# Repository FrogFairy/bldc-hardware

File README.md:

## Schematic top level

## Layout -made with KiCad!-

## 3D views

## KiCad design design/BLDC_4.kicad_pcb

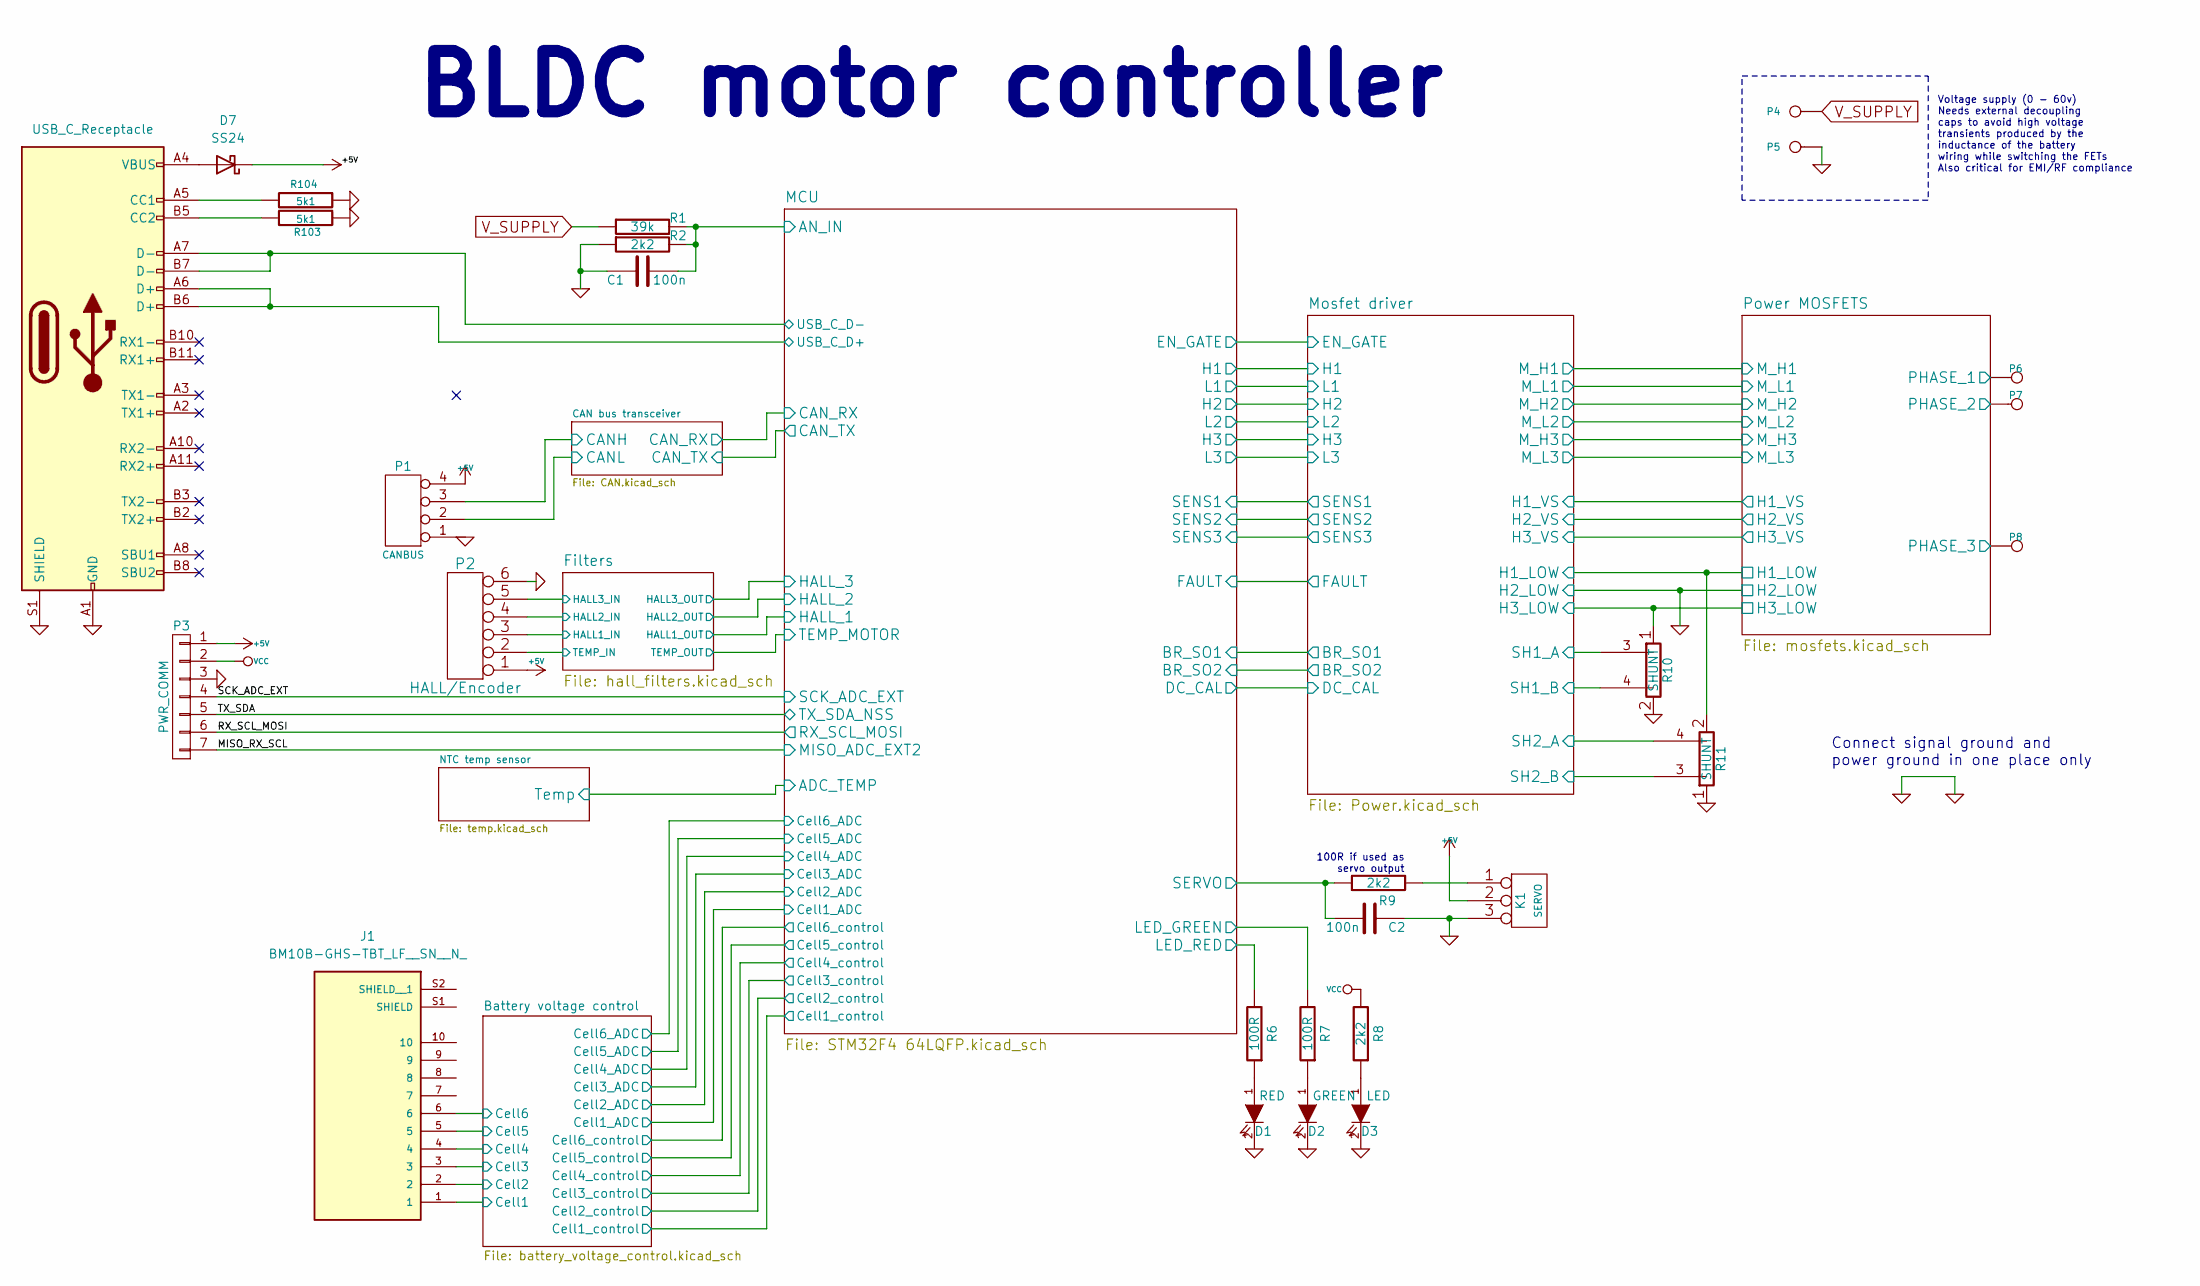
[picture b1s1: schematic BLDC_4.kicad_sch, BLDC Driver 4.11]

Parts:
C1, C2: 100n; SMD-0603_c
D1: RED; LED-0603
D2: GREEN; LED-0603
D3: LED; LED-0603
D7: SS24; D_SMA
J1: BM10B-GHS-TBT_LF__SN__N_; JST_BM10B-GHS-TBT_LF__SN__N_; PARTREV N/A
J2: USB_C_Receptacle
K1: SERVO; pinhead-1X03
P1: CANBUS; b4b-ph-kl
P2: HALL/Encoder; MICRO_JST_6
P3: PWR_COMM; b7b-ph-kl
P4: IN+; 1PAD_4x5mm
P5: IN-; 1PAD_4x5mm
P6: MOTOR3; 1PAD_4x5mm
P7: MOTOR2; 1PAD_4x5mm
P8: MOTOR1; 1PAD_4x5mm
R1: 39k; SMD-0603_r
R2, R8, R9: 2k2; SMD-0603_r
R6, R7: 100R; SMD-0603_r
R10, R11: SHUNT; WSLP2726
R103, R104: 5k1; SMD-0603_r

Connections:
+5V: D7.1 (K), K1.2 (PM), P1.4, P2.1, P3.1; also elsewhere on the board
/Battery voltage control/Cell1: J1.1; also elsewhere on the board
/Battery voltage control/Cell2: J1.2; also elsewhere on the board
/Battery voltage control/Cell3: J1.3; also elsewhere on the board
/Battery voltage control/Cell4: J1.4; also elsewhere on the board
/Battery voltage control/Cell5: J1.5; also elsewhere on the board
/Battery voltage control/Cell6: J1.6; also elsewhere on the board
/CAN bus transceiver/CANH: P1.3; also elsewhere on the board
/CAN bus transceiver/CANL: P1.2; also elsewhere on the board
/Filters/HALL1_IN: P2.3; also elsewhere on the board
/Filters/HALL2_IN: P2.4; also elsewhere on the board
/Filters/HALL3_IN: P2.5; also elsewhere on the board
/Filters/TEMP_MOTOR: P2.2; also elsewhere on the board
/MCU/AN_IN: C1.2, R1.2, R2.2; also elsewhere on the board
/MCU/LED_GREEN: R7.2; also elsewhere on the board
/MCU/LED_RED: R6.2; also elsewhere on the board
/MCU/SERVO: C2.2, R9.1; also elsewhere on the board
/MISO_RX_SCL: P3.7; also elsewhere on the board
/Mosfet driver/H1_LOW: R11.2; also elsewhere on the board
/Mosfet driver/H1_VS: P6.1; also elsewhere on the board
/Mosfet driver/H2_VS: P7.1; also elsewhere on the board
/Mosfet driver/H3_LOW: R10.1; also elsewhere on the board
/Mosfet driver/H3_VS: P8.1; also elsewhere on the board
/Mosfet driver/SH1_A: R10.3; also elsewhere on the board
/Mosfet driver/SH1_B: R10.4; also elsewhere on the board
/Mosfet driver/SH2_A: R11.4; also elsewhere on the board
/Mosfet driver/SH2_B: R11.3; also elsewhere on the board
/RX_SCL_MOSI: P3.6; also elsewhere on the board
/SCK_ADC_EXT: P3.4; also elsewhere on the board
/TX_SDA: P3.5; also elsewhere on the board
GND: C1.1, C2.1, D1.2 (K), D2.2 (K), D3.2 (K), J2.A1 (GND), J2.A12 (GND), J2.B1 (GND), J2.B12 (GND), J2.S1 (SHIELD), K1.3, P1.1, P2.6, P3.3, P5.1, R2.1, R10.2, R11.1, R103.1, R104.1; also elsewhere on the board
unnamed: D1.1 (A), R6.1
unnamed: D2.1 (A), R7.1
unnamed: D3.1 (A), R8.1
unnamed: D7.2 (A), J2.A4 (VBUS), J2.A9 (VBUS), J2.B4 (VBUS), J2.B9 (VBUS)
unnamed: J2.A5 (CC1), R104.2
unnamed: J2.B5 (CC2), R103.2
unnamed: J2.A6 (D+), J2.B6 (D+)
unnamed: J2.A7 (D-), J2.B7 (D-)
unnamed: K1.1, R9.2
VCC: P3.2, R8.2; also elsewhere on the board
V_SUPPLY: P4.1, R1.1; also elsewhere on the board

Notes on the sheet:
Voltage supply (0 - 60v) Needs external decoupling caps to avoid high voltage transients produced by the inductance of the battery wiring while switching the FETs Also critical for EMI/RF compliance
Connect signal ground and power ground in one place only
BLDC motor controller
100R if used as servo output

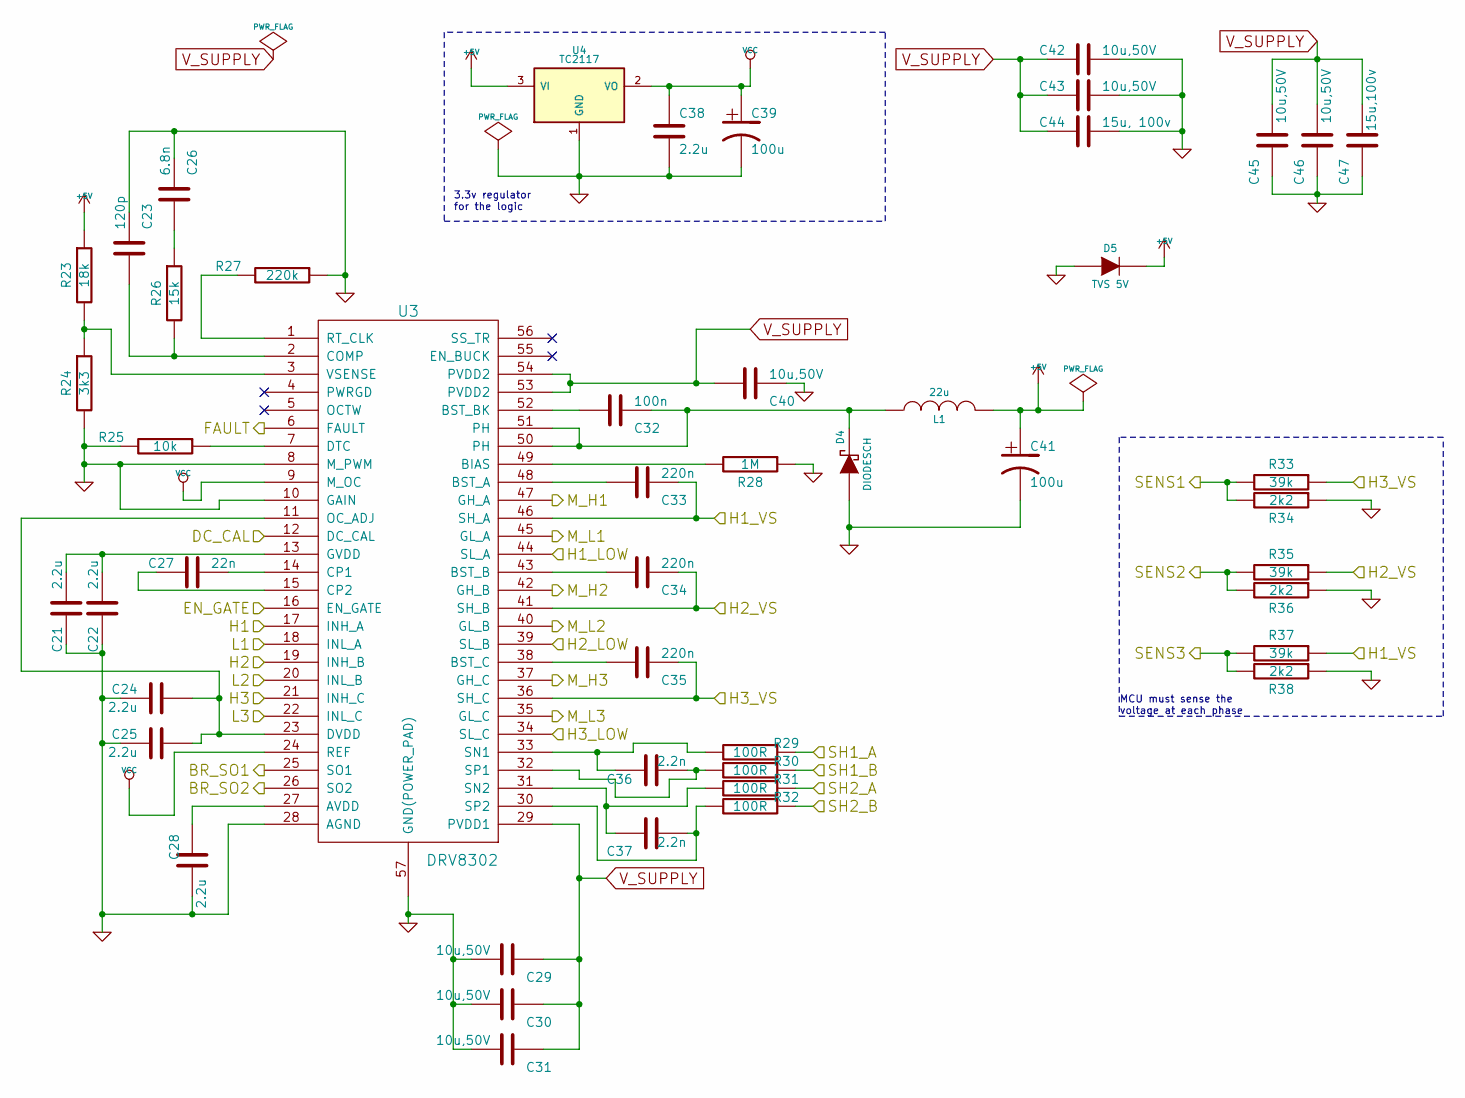
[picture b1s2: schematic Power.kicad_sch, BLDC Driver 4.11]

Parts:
C21, C22, C24, C25, C28, C38: 2.2u; SMD-0603_c
C23: 120p; SMD-0603_c
C26: 6.8n; SMD-0603_c
C27: 22n; SMD-0603_c
C29, C30, C31, C40, C42, C43, C45, C46: 10u,50V; SMD-1206
C32: 100n; SMD-0603_c
C33, C34, C35: 220n; SMD-0603_c
C36, C37: 2.2n; SMD-0603_c
C39, C41: 100u; c_tant_B
C44: 15u, 100v; c_2220
C47: 15u,100v; c_2220
D4: DIODESCH; SMA_Handsoldering
D5: TVS 5V; do214ac
L1: 22u; inductor_smd_8x5mm
R23: 18k; SMD-0603_r
R24: 3k3; SMD-0603_r
R25: 10k; SMD-0603_r
R26: 15k; SMD-0603_r
R27: 220k; SMD-0603_r
R28: 1M; SMD-0603_r
R29, R30, R31, R32: 100R; SMD-0603_r
R33, R35, R37: 39k; SMD-0603_r
R34, R36, R38: 2k2; SMD-0603_r
U3: DRV8302; TSSOP-56-PP
U4: TC2117; SOT-223

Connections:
+5V: C41.1, D5.2 (K), L1.2, R23.1, U4.3 (VI); also elsewhere on the board
/MCU/BR_SO1: U3.25 (SO1); also elsewhere on the board
/MCU/BR_SO2: U3.26 (SO2); also elsewhere on the board
/MCU/DC_CAL: U3.12 (DC_CAL); also elsewhere on the board
/MCU/EN_GATE: U3.16 (EN_GATE); also elsewhere on the board
/MCU/FAULT: U3.6 (FAULT); also elsewhere on the board
/MCU/H1: U3.17 (INH_A); also elsewhere on the board
/MCU/H2: U3.19 (INH_B); also elsewhere on the board
/MCU/H3: U3.21 (INH_C); also elsewhere on the board
/MCU/L1: U3.18 (INL_A); also elsewhere on the board
/MCU/L2: U3.20 (INL_B); also elsewhere on the board
/MCU/L3: U3.22 (INL_C); also elsewhere on the board
/MCU/SENS1: R33.2, R34.2; also elsewhere on the board
/MCU/SENS2: R35.2, R36.2; also elsewhere on the board
/MCU/SENS3: R37.2, R38.2; also elsewhere on the board
/Mosfet driver/H1_LOW: U3.44 (SL_A); also elsewhere on the board
/Mosfet driver/H1_VS: C33.1, R37.1, U3.46 (SH_A); also elsewhere on the board
/Mosfet driver/H2_VS: C34.1, R35.1, U3.41 (SH_B); also elsewhere on the board
/Mosfet driver/H3_LOW: U3.34 (SL_C); also elsewhere on the board
/Mosfet driver/H3_VS: C35.1, R33.1, U3.36 (SH_C); also elsewhere on the board
/Mosfet driver/M_H1: U3.47 (GH_A); also elsewhere on the board
/Mosfet driver/M_H2: U3.42 (GH_B); also elsewhere on the board
/Mosfet driver/M_H3: U3.37 (GH_C); also elsewhere on the board
/Mosfet driver/M_L1: U3.45 (GL_A); also elsewhere on the board
/Mosfet driver/M_L2: U3.40 (GL_B); also elsewhere on the board
/Mosfet driver/M_L3: U3.35 (GL_C); also elsewhere on the board
/Mosfet driver/SH1_A: R29.1; also elsewhere on the board
/Mosfet driver/SH1_B: R30.1; also elsewhere on the board
/Mosfet driver/SH2_A: R31.1; also elsewhere on the board
/Mosfet driver/SH2_B: R32.1; also elsewhere on the board
GND: C21.2, C22.2, C23.1, C24.1, C25.1, C26.1, C28.1, C29.2, C30.2, C31.2, C38.2, C39.2, C40.1, C41.2, C42.1, C43.1, C44.1, C45.1, C46.1, C47.1, D4.1 (A), D5.1 (A), R24.2, R25.2, R27.1, R28.1, R34.1, R36.1, R38.1, U3.8 (M_PWM), U3.10 (GAIN), U3.28 (AGND), U3.39 (SL_B), U3.57 (GND(POWER_PAD)), U4.1 (GND); also elsewhere on the board
unnamed: C26.2, R26.1
unnamed: C32.1, D4.2 (K), L1.1, U3.50 (PH), U3.51 (PH)
unnamed: C28.2, U3.27 (AVDD)
unnamed: R28.2, U3.49 (BIAS)
unnamed: C33.2, U3.48 (BST_A)
unnamed: C34.2, U3.43 (BST_B)
unnamed: C32.2, U3.52 (BST_BK)
unnamed: C35.2, U3.38 (BST_C)
unnamed: C23.2, R26.2, U3.2 (COMP)
unnamed: C27.1, U3.14 (CP1)
unnamed: C27.2, U3.15 (CP2)
unnamed: R25.1, U3.7 (DTC)
unnamed: C24.2, C25.2, U3.11 (OC_ADJ), U3.23 (DVDD)
unnamed: C21.1, C22.1, U3.13 (GVDD)
unnamed: R27.2, U3.1 (RT_CLK)
unnamed: C36.1, R29.2, U3.33 (SN1)
unnamed: C37.1, R31.2, U3.31 (SN2)
unnamed: C36.2, R30.2, U3.32 (SP1)
unnamed: C37.2, R32.2, U3.30 (SP2)
unnamed: R23.2, R24.1, U3.3 (VSENSE)
VCC: C38.1, C39.1, U3.9 (M_OC), U3.24 (REF), U4.2 (VO); also elsewhere on the board
V_SUPPLY: C29.1, C30.1, C31.1, C40.2, C42.2, C43.2, C44.2, C45.2, C46.2, C47.2, U3.29 (PVDD1), U3.53 (PVDD2), U3.54 (PVDD2); also elsewhere on the board

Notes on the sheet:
MCU must sense the voltage at each phase
3.3v regulator for the logic

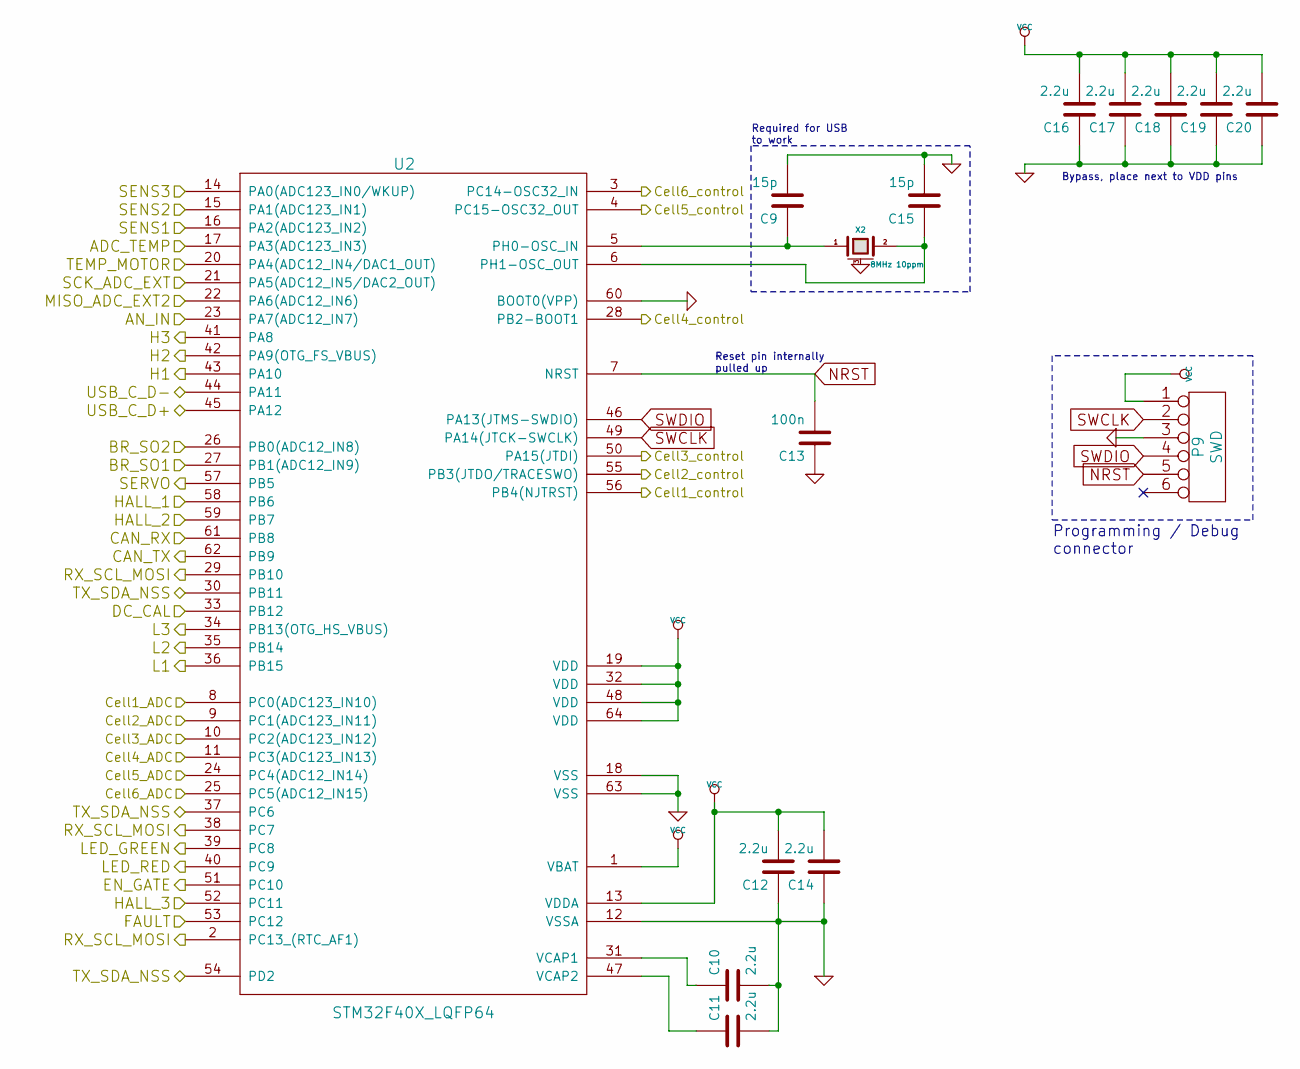
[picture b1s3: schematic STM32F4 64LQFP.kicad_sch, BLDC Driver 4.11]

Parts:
C9, C15: 15p; SMD-0603_c
C10, C11, C12, C14, C16, C17, C18, C19, C20: 2.2u; SMD-0603_c
C13: 100n; SMD-0603_c
P9: SWD; MICRO_JST_6
U2: STM32F40X_LQFP64; lqfp64_pad_mod
X2: 8MHz 10ppm; Crystal_5x3mm; mfg# ABM3B-8.0-10-1UT

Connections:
/Battery voltage control/Cell1_ADC: U2.8 (PC0(ADC123_IN10)); also elsewhere on the board
/Battery voltage control/Cell1_control: U2.56 (PB4(NJTRST)); also elsewhere on the board
/Battery voltage control/Cell2_ADC: U2.9 (PC1(ADC123_IN11)); also elsewhere on the board
/Battery voltage control/Cell2_control: U2.55 (PB3(JTDO/TRACESWO)); also elsewhere on the board
/Battery voltage control/Cell3_ADC: U2.10 (PC2(ADC123_IN12)); also elsewhere on the board
/Battery voltage control/Cell3_control: U2.50 (PA15(JTDI)); also elsewhere on the board
/Battery voltage control/Cell4_ADC: U2.11 (PC3(ADC123_IN13)); also elsewhere on the board
/Battery voltage control/Cell4_control: U2.28 (PB2-BOOT1); also elsewhere on the board
/Battery voltage control/Cell5_ADC: U2.24 (PC4(ADC12_IN14)); also elsewhere on the board
/Battery voltage control/Cell5_control: U2.4 (PC15-OSC32_OUT); also elsewhere on the board
/Battery voltage control/Cell6_ADC: U2.25 (PC5(ADC12_IN15)); also elsewhere on the board
/Battery voltage control/Cell6_control: U2.3 (PC14-OSC32_IN); also elsewhere on the board
/CAN bus transceiver/CAN_RX: U2.61 (PB8); also elsewhere on the board
/CAN bus transceiver/CAN_TX: U2.62 (PB9); also elsewhere on the board
/Filters/HALL1_OUT: U2.58 (PB6); also elsewhere on the board
/Filters/HALL2_OUT: U2.59 (PB7); also elsewhere on the board
/Filters/HALL3_OUT: U2.52 (PC11); also elsewhere on the board
/Filters/TEMP_MOTOR: U2.20 (PA4(ADC12_IN4/DAC1_OUT)); also elsewhere on the board
/MCU/ADC_TEMP: U2.17 (PA3(ADC123_IN3)); also elsewhere on the board
/MCU/AN_IN: U2.23 (PA7(ADC12_IN7)); also elsewhere on the board
/MCU/BR_SO1: U2.27 (PB1(ADC12_IN9)); also elsewhere on the board
/MCU/BR_SO2: U2.26 (PB0(ADC12_IN8)); also elsewhere on the board
/MCU/DC_CAL: U2.33 (PB12); also elsewhere on the board
/MCU/EN_GATE: U2.51 (PC10); also elsewhere on the board
/MCU/FAULT: U2.53 (PC12); also elsewhere on the board
/MCU/H1: U2.43 (PA10); also elsewhere on the board
/MCU/H2: U2.42 (PA9(OTG_FS_VBUS)); also elsewhere on the board
/MCU/H3: U2.41 (PA8); also elsewhere on the board
/MCU/L1: U2.36 (PB15); also elsewhere on the board
/MCU/L2: U2.35 (PB14); also elsewhere on the board
/MCU/L3: U2.34 (PB13(OTG_HS_VBUS)); also elsewhere on the board
/MCU/LED_GREEN: U2.39 (PC8); also elsewhere on the board
/MCU/LED_RED: U2.40 (PC9); also elsewhere on the board
/MCU/SENS1: U2.16 (PA2(ADC123_IN2)); also elsewhere on the board
/MCU/SENS2: U2.15 (PA1(ADC123_IN1)); also elsewhere on the board
/MCU/SENS3: U2.14 (PA0(ADC123_IN0/WKUP)); also elsewhere on the board
/MCU/SERVO: U2.57 (PB5); also elsewhere on the board
/MCU/USB_C_D+: U2.45 (PA12)
/MCU/USB_C_D-: U2.44 (PA11)
/MISO_RX_SCL: U2.22 (PA6(ADC12_IN6)); also elsewhere on the board
/RX_SCL_MOSI: U2.2 (PC13_(RTC_AF1)), U2.29 (PB10), U2.38 (PC7); also elsewhere on the board
/SCK_ADC_EXT: U2.21 (PA5(ADC12_IN5/DAC2_OUT)); also elsewhere on the board
/TX_SDA: U2.30 (PB11), U2.37 (PC6), U2.54 (PD2); also elsewhere on the board
GND: C9.2, C10.2, C11.2, C12.1, C13.1, C14.1, C15.2, C16.1, C17.1, C18.1, C19.1, C20.1, P9.3, U2.12 (VSSA), U2.18 (VSS), U2.60 (BOOT0(VPP)), U2.63 (VSS), X2.3 (case); also elsewhere on the board
NRST: C13.2, P9.5, U2.7 (NRST)
unnamed: C9.1, U2.5 (PH0-OSC_IN), X2.1
unnamed: C15.1, U2.6 (PH1-OSC_OUT), X2.2
unnamed: C10.1, U2.31 (VCAP1)
unnamed: C11.1, U2.47 (VCAP2)
SWCLK: P9.2, U2.49 (PA14(JTCK-SWCLK))
SWDIO: P9.4, U2.46 (PA13(JTMS-SWDIO))
VCC: C12.2, C14.2, C16.2, C17.2, C18.2, C19.2, C20.2, P9.1, U2.1 (VBAT), U2.13 (VDDA), U2.19 (VDD), U2.32 (VDD), U2.48 (VDD), U2.64 (VDD); also elsewhere on the board

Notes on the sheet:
Reset pin internally pulled up
Required for USB to work
Programming / Debug connector
Bypass, place next to VDD pins

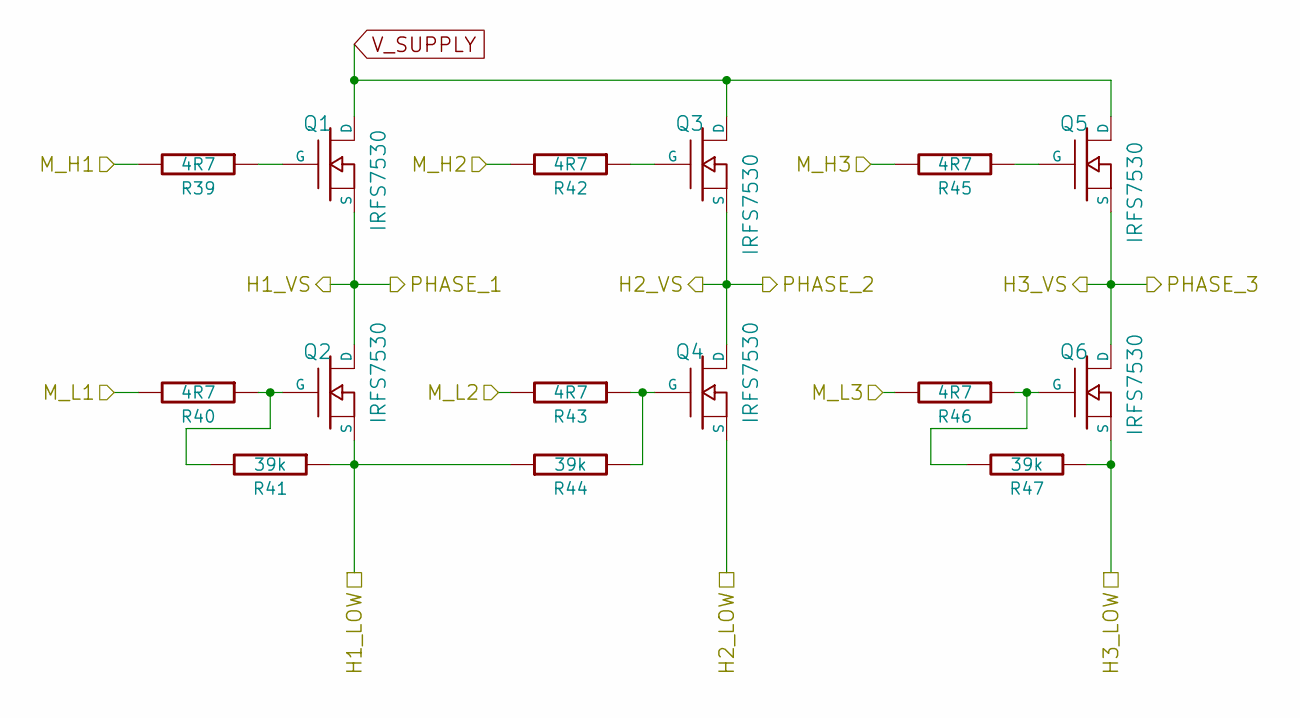
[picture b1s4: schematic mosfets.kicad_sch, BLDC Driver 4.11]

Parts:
Q1, Q2, Q3, Q4, Q5, Q6: IRFS7530; D2PAK-7-GDS
R39, R40, R42, R43, R45, R46: 4R7; SMD-0603_r
R41, R44, R47: 39k; SMD-0603_r

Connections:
/Mosfet driver/H1_LOW: Q2.S, R41.1, R44.1; also elsewhere on the board
/Mosfet driver/H1_VS: Q1.S, Q2.D; also elsewhere on the board
/Mosfet driver/H2_VS: Q3.S, Q4.D; also elsewhere on the board
/Mosfet driver/H3_LOW: Q6.S, R47.1; also elsewhere on the board
/Mosfet driver/H3_VS: Q5.S, Q6.D; also elsewhere on the board
/Mosfet driver/M_H1: R39.2; also elsewhere on the board
/Mosfet driver/M_H2: R42.2; also elsewhere on the board
/Mosfet driver/M_H3: R45.2; also elsewhere on the board
/Mosfet driver/M_L1: R40.2; also elsewhere on the board
/Mosfet driver/M_L2: R43.2; also elsewhere on the board
/Mosfet driver/M_L3: R46.2; also elsewhere on the board
GND: Q4.S; also elsewhere on the board
unnamed: Q1.G, R39.1
unnamed: Q2.G, R40.1, R41.2
unnamed: Q3.G, R42.1
unnamed: Q4.G, R43.1, R44.2
unnamed: Q5.G, R45.1
unnamed: Q6.G, R46.1, R47.2
V_SUPPLY: Q1.D, Q3.D, Q5.D; also elsewhere on the board

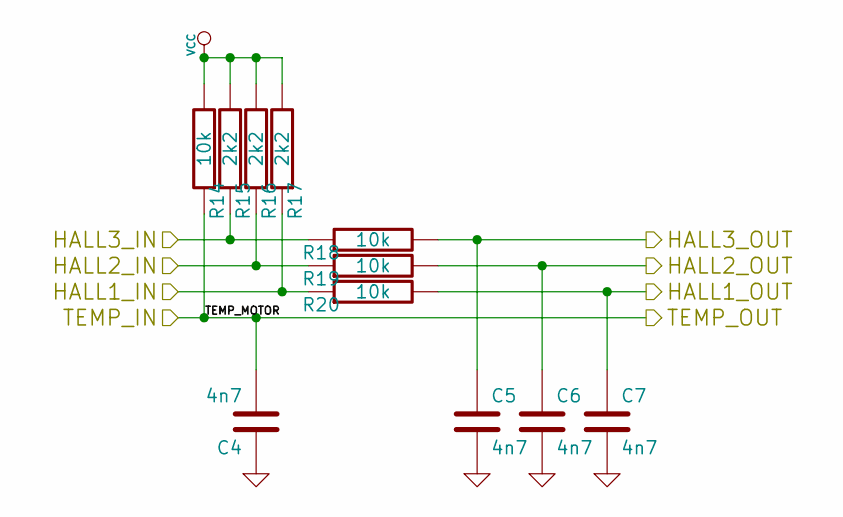
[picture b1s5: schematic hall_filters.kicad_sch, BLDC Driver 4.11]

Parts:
C4, C5, C6, C7: 4n7; SMD-0603_c
R14, R18, R19, R20: 10k; SMD-0603_r
R15, R16, R17: 2k2; SMD-0603_r

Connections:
/Filters/HALL1_IN: R17.1, R20.1; also elsewhere on the board
/Filters/HALL1_OUT: C7.1, R20.2; also elsewhere on the board
/Filters/HALL2_IN: R16.1, R19.1; also elsewhere on the board
/Filters/HALL2_OUT: C6.1, R19.2; also elsewhere on the board
/Filters/HALL3_IN: R15.1, R18.1; also elsewhere on the board
/Filters/HALL3_OUT: C5.1, R18.2; also elsewhere on the board
/Filters/TEMP_MOTOR: C4.2, R14.1; also elsewhere on the board
GND: C4.1, C5.2, C6.2, C7.2; also elsewhere on the board
VCC: R14.2, R15.2, R16.2, R17.2; also elsewhere on the board

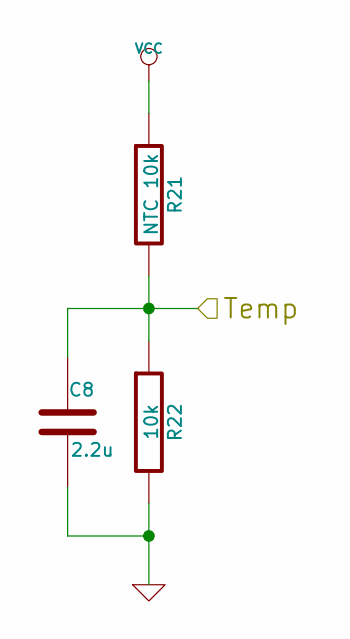
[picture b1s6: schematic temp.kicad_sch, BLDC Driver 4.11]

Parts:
C8: 2.2u; SMD-0603_c
R21: NTC 10k; SMD-0603_r
R22: 10k; SMD-0603_r

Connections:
/MCU/ADC_TEMP: C8.1, R21.2, R22.1; also elsewhere on the board
GND: C8.2, R22.2; also elsewhere on the board
VCC: R21.1; also elsewhere on the board

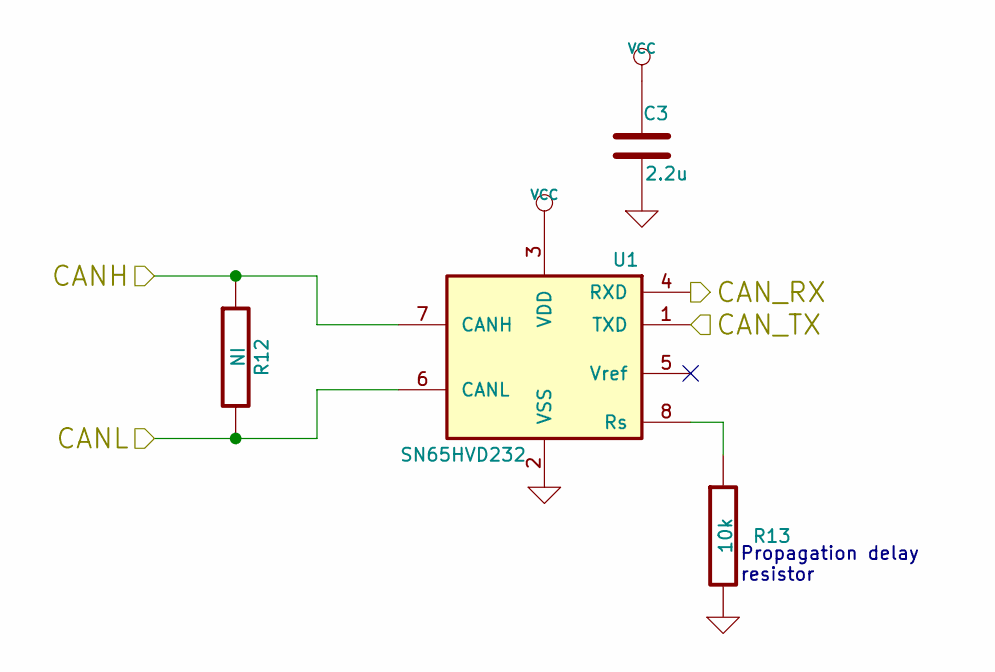
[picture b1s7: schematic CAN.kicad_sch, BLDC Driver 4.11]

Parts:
C3: 2.2u; SMD-0603_c
R12: NI; SMD-0603_r
R13: 10k; SMD-0603_r
U1: SN65HVD232; SOIC-8-W

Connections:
/CAN bus transceiver/CANH: R12.1, U1.7 (CANH); also elsewhere on the board
/CAN bus transceiver/CANL: R12.2, U1.6 (CANL); also elsewhere on the board
/CAN bus transceiver/CAN_RX: U1.4 (RXD); also elsewhere on the board
/CAN bus transceiver/CAN_TX: U1.1 (TXD); also elsewhere on the board
GND: C3.2, R13.2, U1.2 (VSS); also elsewhere on the board
unnamed: R13.1, U1.8 (Rs)
VCC: C3.1, U1.3 (VDD); also elsewhere on the board

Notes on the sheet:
Propagation delay resistor

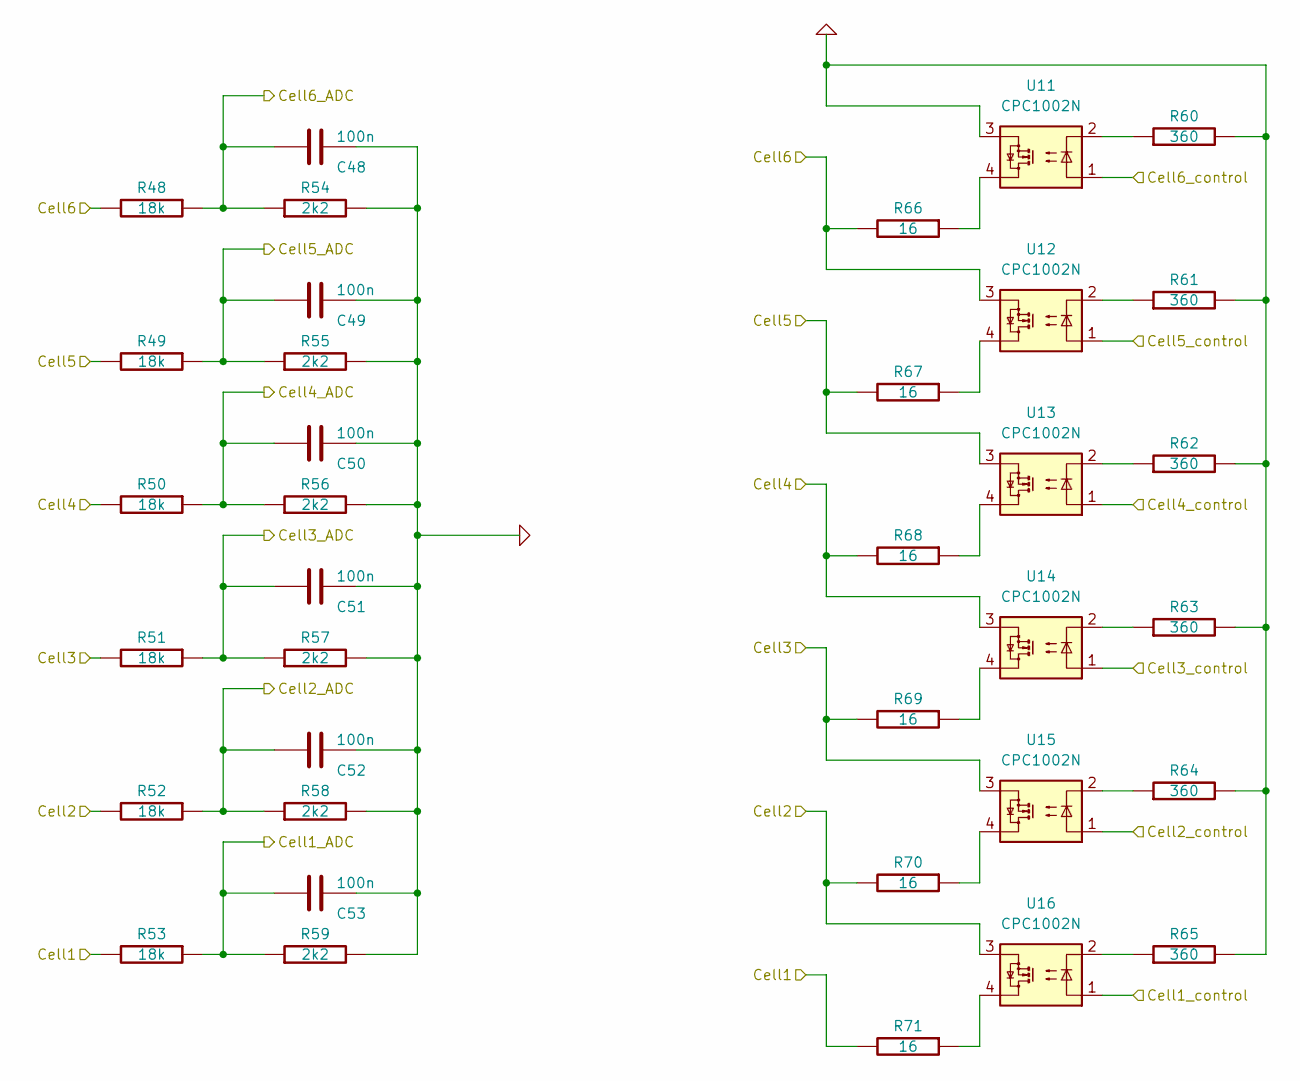
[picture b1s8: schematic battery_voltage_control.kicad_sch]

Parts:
C48, C49, C50, C51, C52, C53: 100n; SMD-0603_c
R48, R49, R50, R51, R52, R53: 18k; SMD-0603_r
R54, R55, R56, R57, R58, R59: 2k2; SMD-0603_r
R60, R61, R62, R63, R64, R65: 360; SMD-0603_r
R66, R67, R68, R69, R70, R71: 16; R_2512_6332Metric
U11, U12, U13, U14, U15, U16: CPC1002N; SOP-4_3.8x4.1mm_P2.54mm

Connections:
/Battery voltage control/Cell1: R53.2, R71.2; also elsewhere on the board
/Battery voltage control/Cell1_ADC: C53.2, R53.1, R59.1; also elsewhere on the board
/Battery voltage control/Cell1_control: U16.1; also elsewhere on the board
/Battery voltage control/Cell2: R52.2, R70.2, U16.3; also elsewhere on the board
/Battery voltage control/Cell2_ADC: C52.2, R52.1, R58.1; also elsewhere on the board
/Battery voltage control/Cell2_control: U15.1; also elsewhere on the board
/Battery voltage control/Cell3: R51.2, R69.2, U15.3; also elsewhere on the board
/Battery voltage control/Cell3_ADC: C51.2, R51.1, R57.1; also elsewhere on the board
/Battery voltage control/Cell3_control: U14.1; also elsewhere on the board
/Battery voltage control/Cell4: R50.2, R68.2, U14.3; also elsewhere on the board
/Battery voltage control/Cell4_ADC: C50.2, R50.1, R56.1; also elsewhere on the board
/Battery voltage control/Cell4_control: U13.1; also elsewhere on the board
/Battery voltage control/Cell5: R49.2, R67.2, U13.3; also elsewhere on the board
/Battery voltage control/Cell5_ADC: C49.2, R49.1, R55.1; also elsewhere on the board
/Battery voltage control/Cell5_control: U12.1; also elsewhere on the board
/Battery voltage control/Cell6: R48.2, R66.2, U12.3; also elsewhere on the board
/Battery voltage control/Cell6_ADC: C48.2, R48.1, R54.1; also elsewhere on the board
/Battery voltage control/Cell6_control: U11.1; also elsewhere on the board
GND: C48.1, C49.1, C50.1, C51.1, C52.1, C53.1, R54.2, R55.2, R56.2, R57.2, R58.2, R59.2, R60.2, R61.2, R62.2, R63.2, R64.2, R65.2, U11.3; also elsewhere on the board
unnamed: R60.1, U11.2
unnamed: R61.1, U12.2
unnamed: R62.1, U13.2
unnamed: R63.1, U14.2
unnamed: R64.1, U15.2
unnamed: R65.1, U16.2
unnamed: R66.1, U11.4
unnamed: R67.1, U12.4
unnamed: R68.1, U13.4
unnamed: R69.1, U14.4
unnamed: R70.1, U15.4
unnamed: R71.1, U16.4

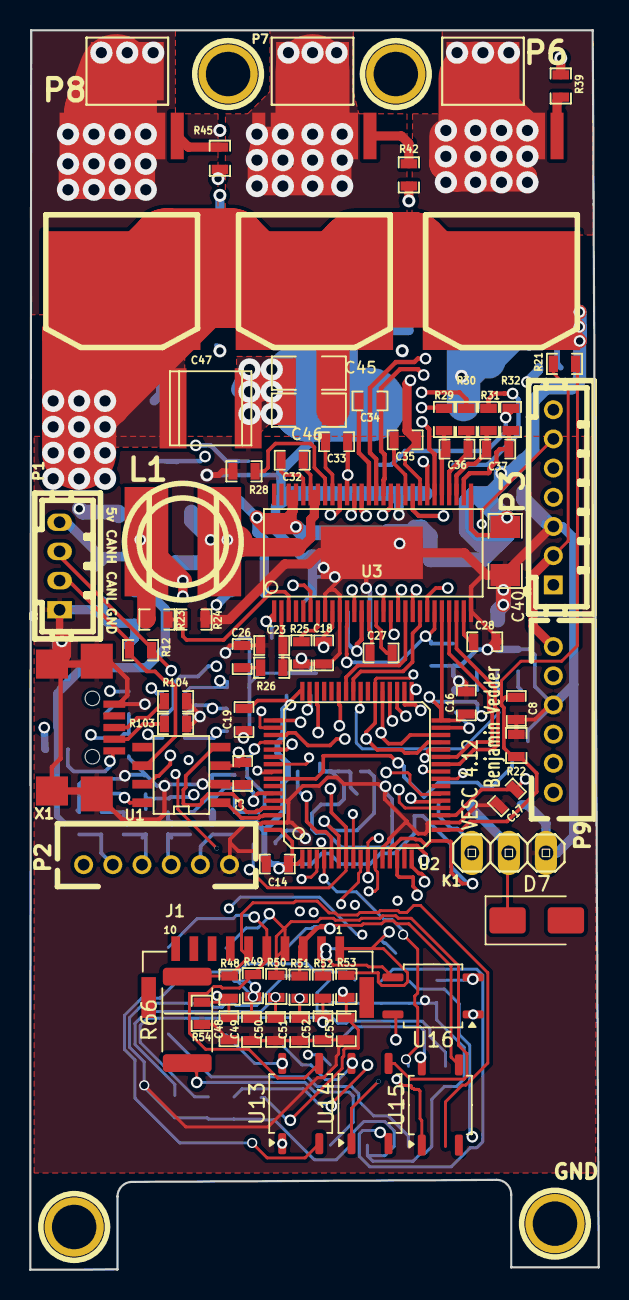
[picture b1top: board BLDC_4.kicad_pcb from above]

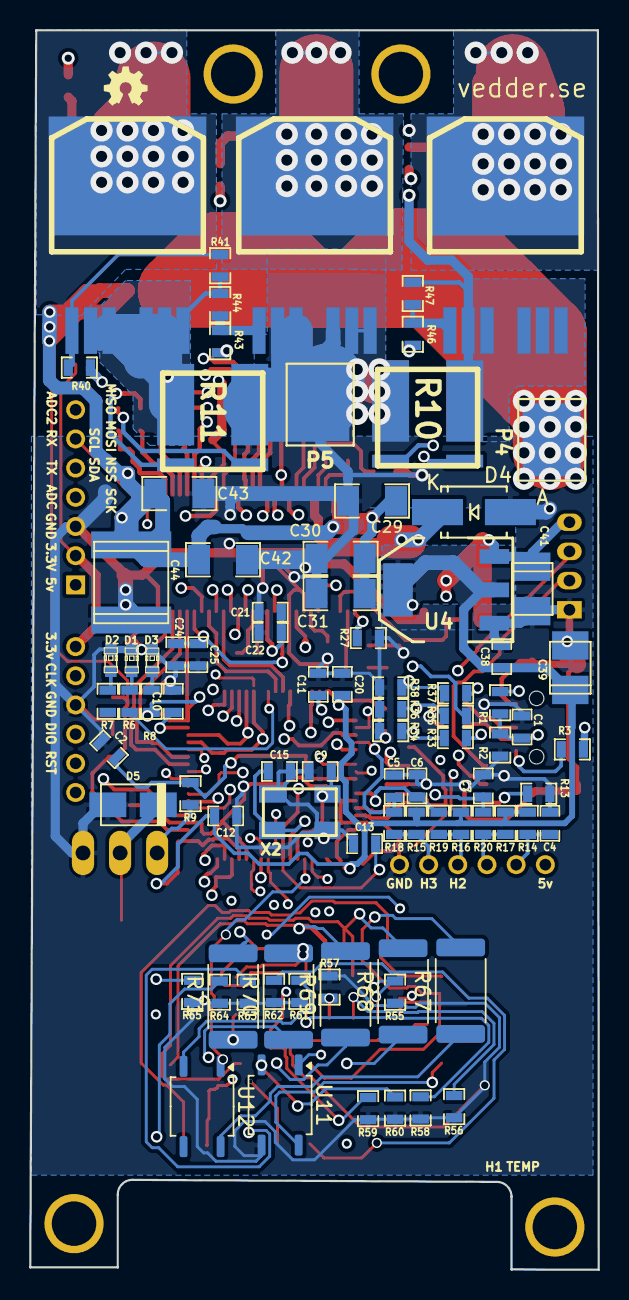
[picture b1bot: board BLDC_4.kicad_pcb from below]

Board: 4 copper layers, 39.0 x 85.0 mm, 164 parts (86 on the bottom side), 122 nets.

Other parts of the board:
1PIN, 1PIN#2, 1PIN#3, 1PIN#4: P***; 1pin
R3: 0R; SMD-0603_r
X1: MINI-USB-SHIELD-32005-201; USB-UX60R-MB-5ST

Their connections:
+5V: R3.2; also elsewhere on the board
GND: X1.5; also elsewhere on the board
unnamed: R3.1, X1.1

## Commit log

2025-04-03 add battery voltage control
2025-04-12 added battery balancer
2025-04-12 change resistance for LED resistors
2025-04-24 added usb connector
2025-04-24 change diod with usb connector
2025-04-24 started pcb tracing
2025-04-24 added new field in components on battery balancer; pcb tracing
2025-05-09 added documentation
